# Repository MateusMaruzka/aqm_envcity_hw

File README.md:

# Air Quality Monitoring Board - EnvCity

## Table of Contents
- [Sensors](#sensors)
- [Powering the board](#powering-the-board)
- [Versions](#versions)
- [Contributing](#contributing)

## Introduction
A detailed explanation of your project, its purpose, and what problem it solves.

## Sensors
Your board supports the following sensors:
- 4 electrochemical sensors
- 1 wind speed sensor
- 1 I2C particulate matter sensor
- 1 DHT11/22 sensor

## Powering the board
Your board supports the following energy sources:
- Solar panel
- Battery
- USB-C

## Versions
There's 2 versions, one it's a 2 layer board and the other it's a 4 layer board (This version could easily be made into a 6 layer board and the fab costs on JLCPCB is the same for 4 or 6 layer boards)

## Contributing
If you have any questions, suggestions, or requests, please send an email to mateusroncaglio@alunos.utfpr.edu.br. We welcome contributions to the project!

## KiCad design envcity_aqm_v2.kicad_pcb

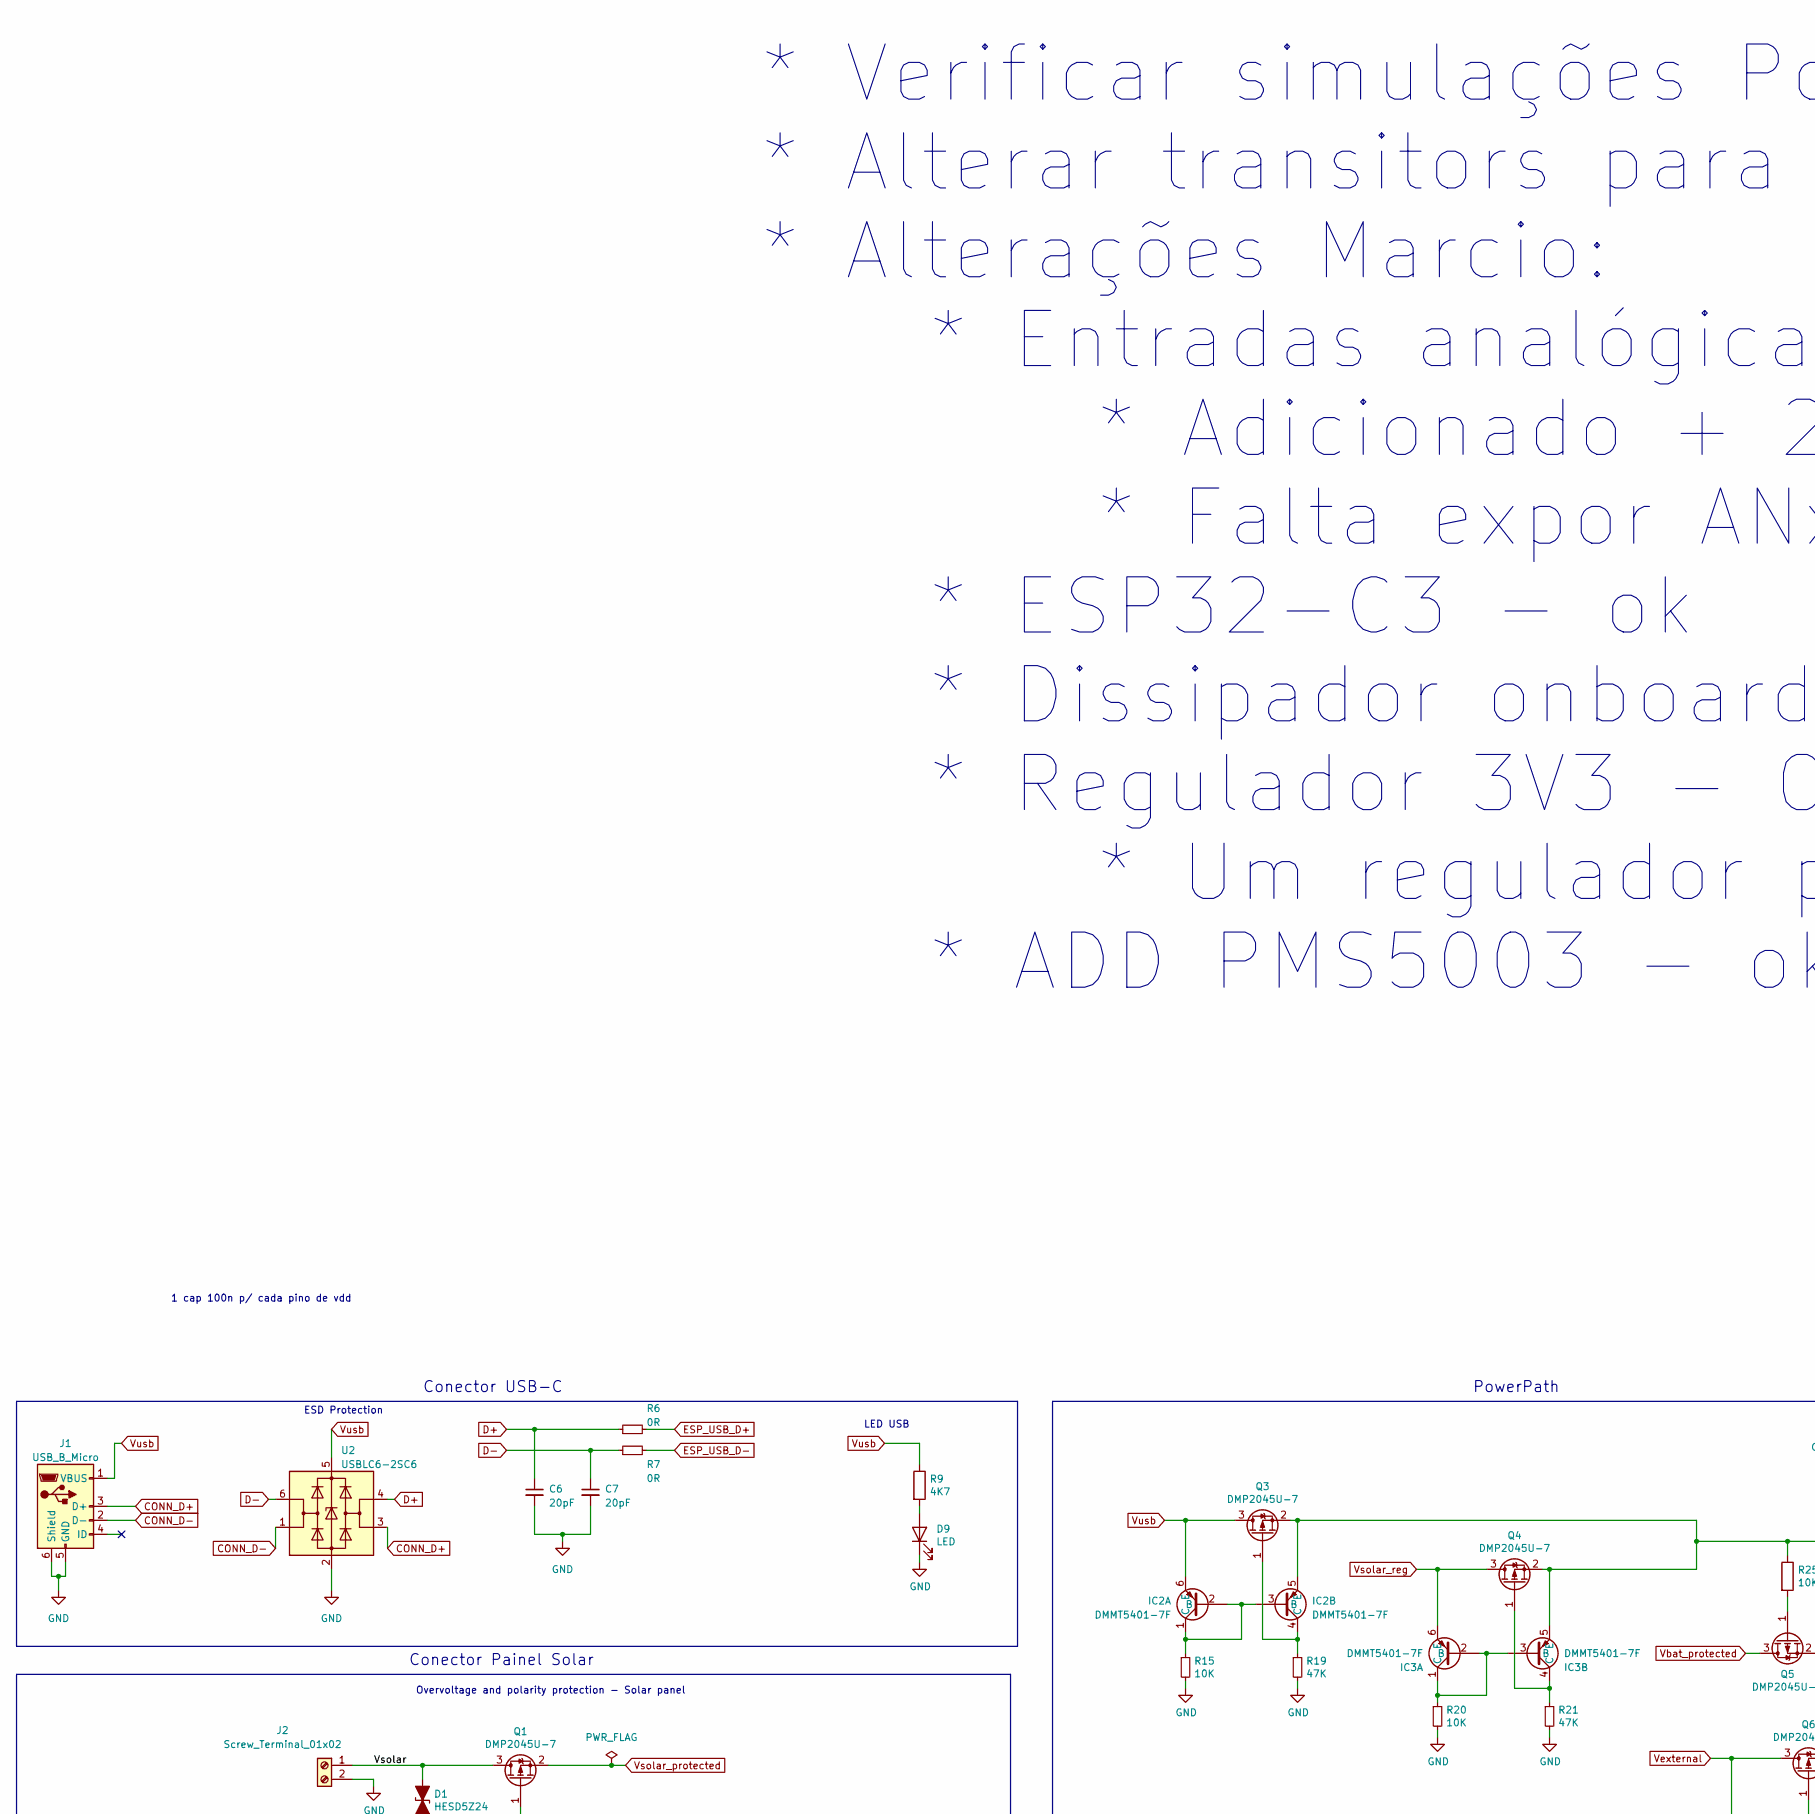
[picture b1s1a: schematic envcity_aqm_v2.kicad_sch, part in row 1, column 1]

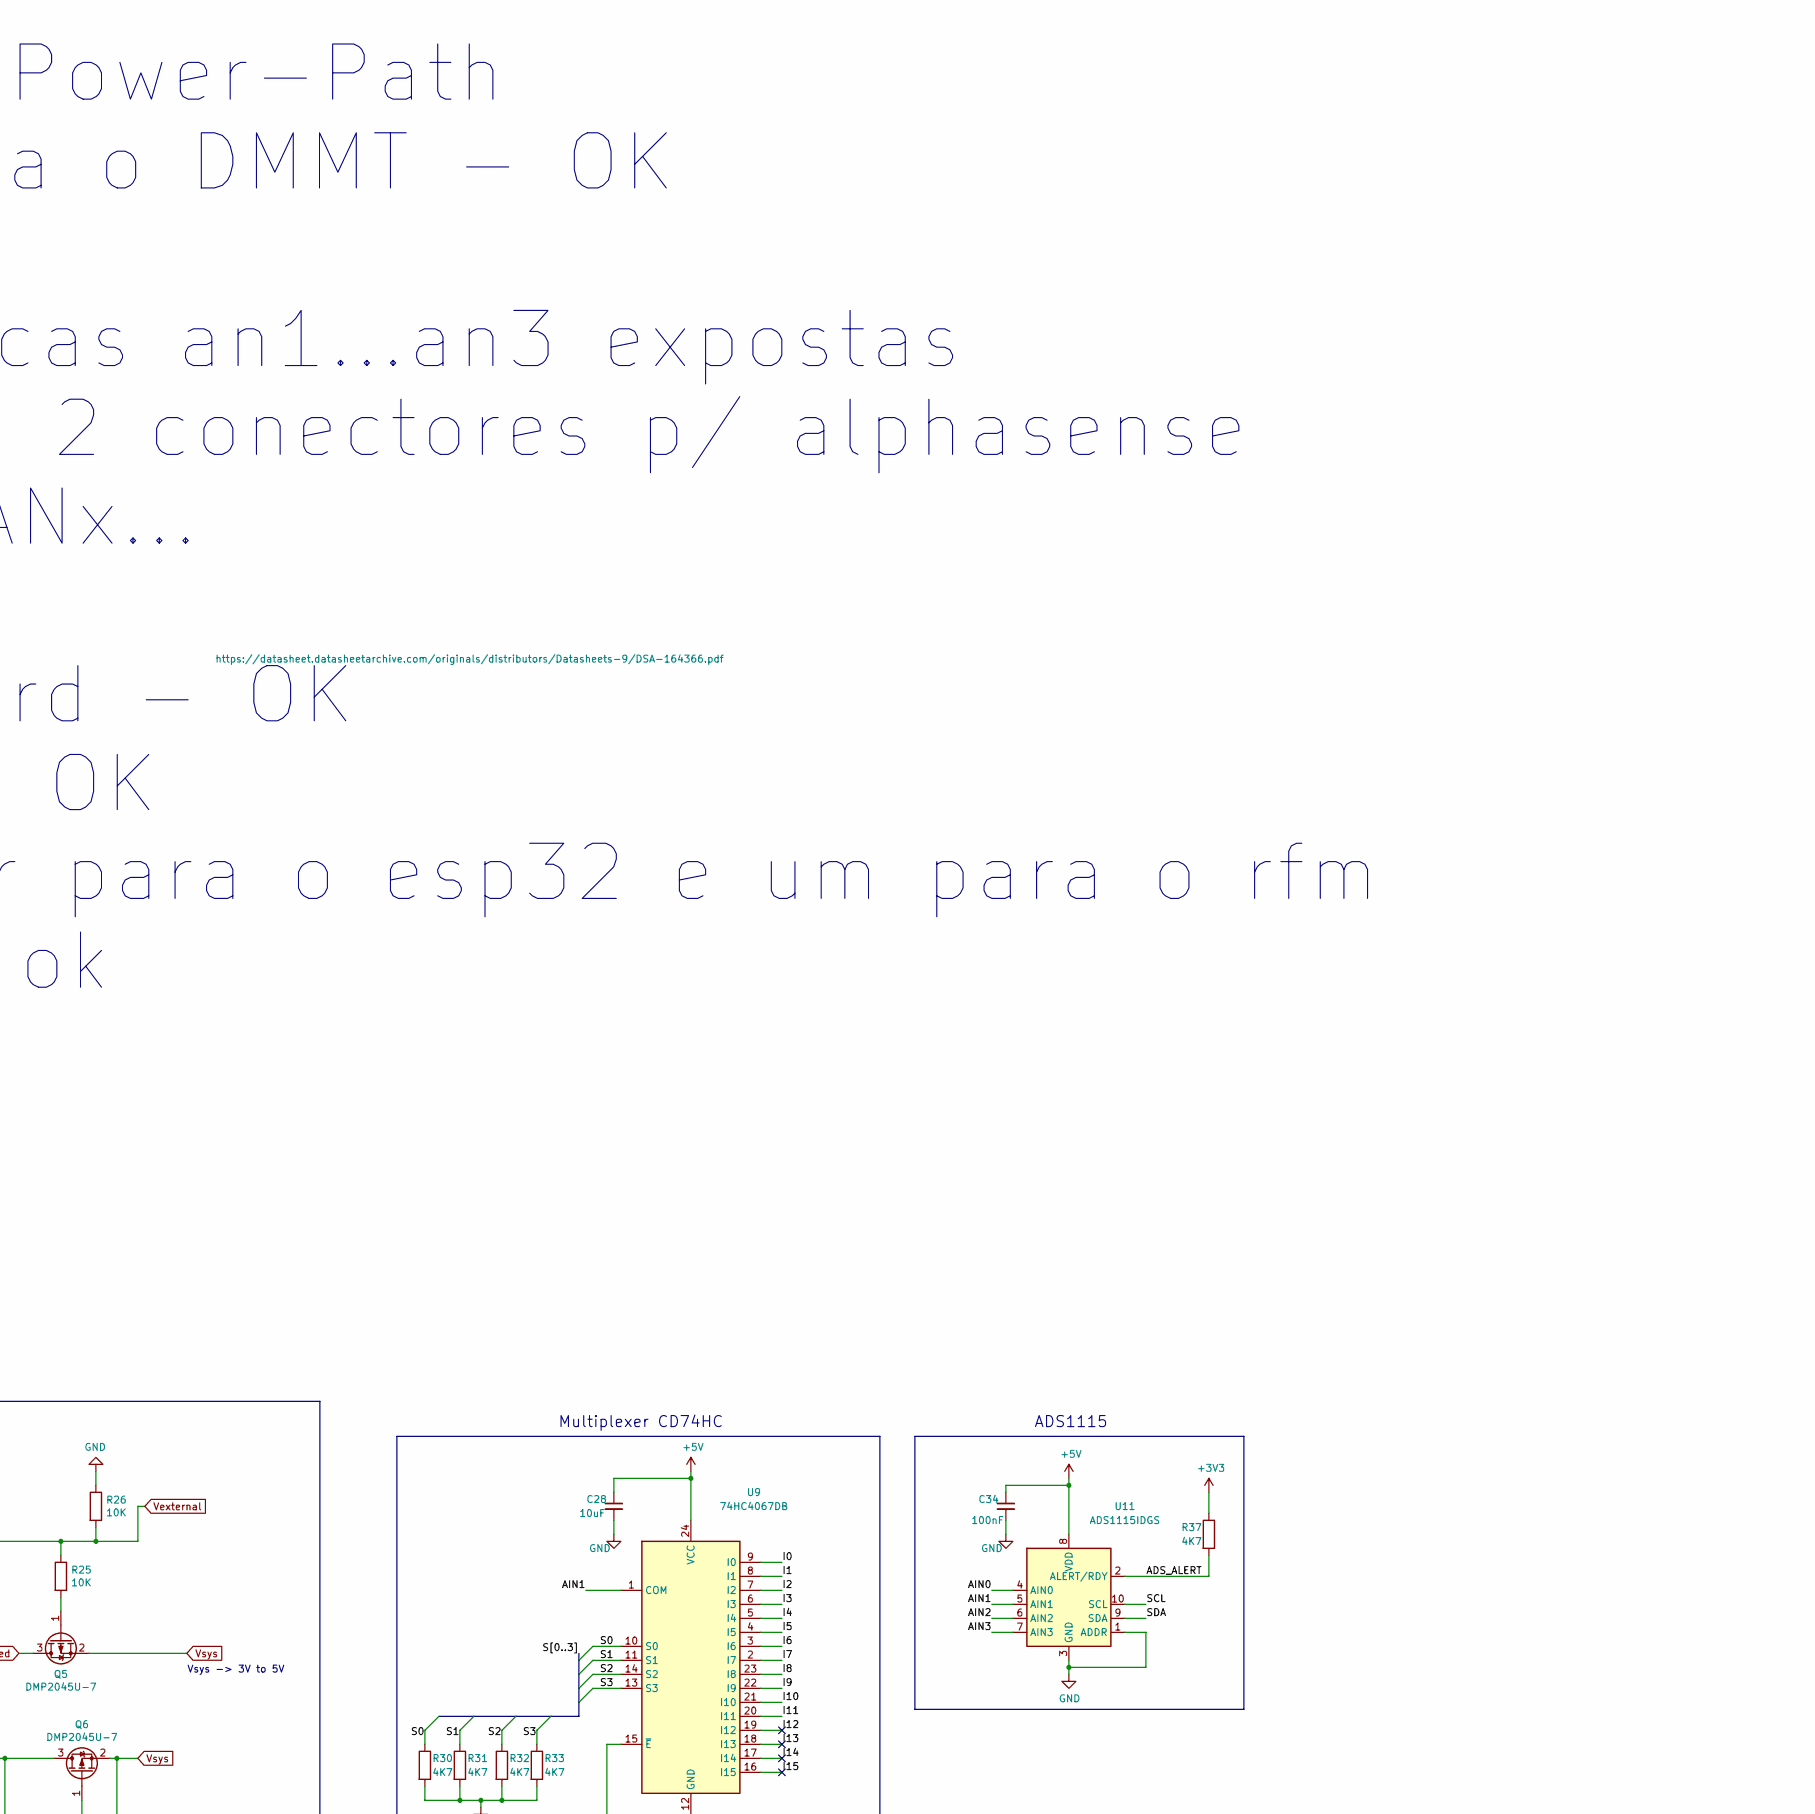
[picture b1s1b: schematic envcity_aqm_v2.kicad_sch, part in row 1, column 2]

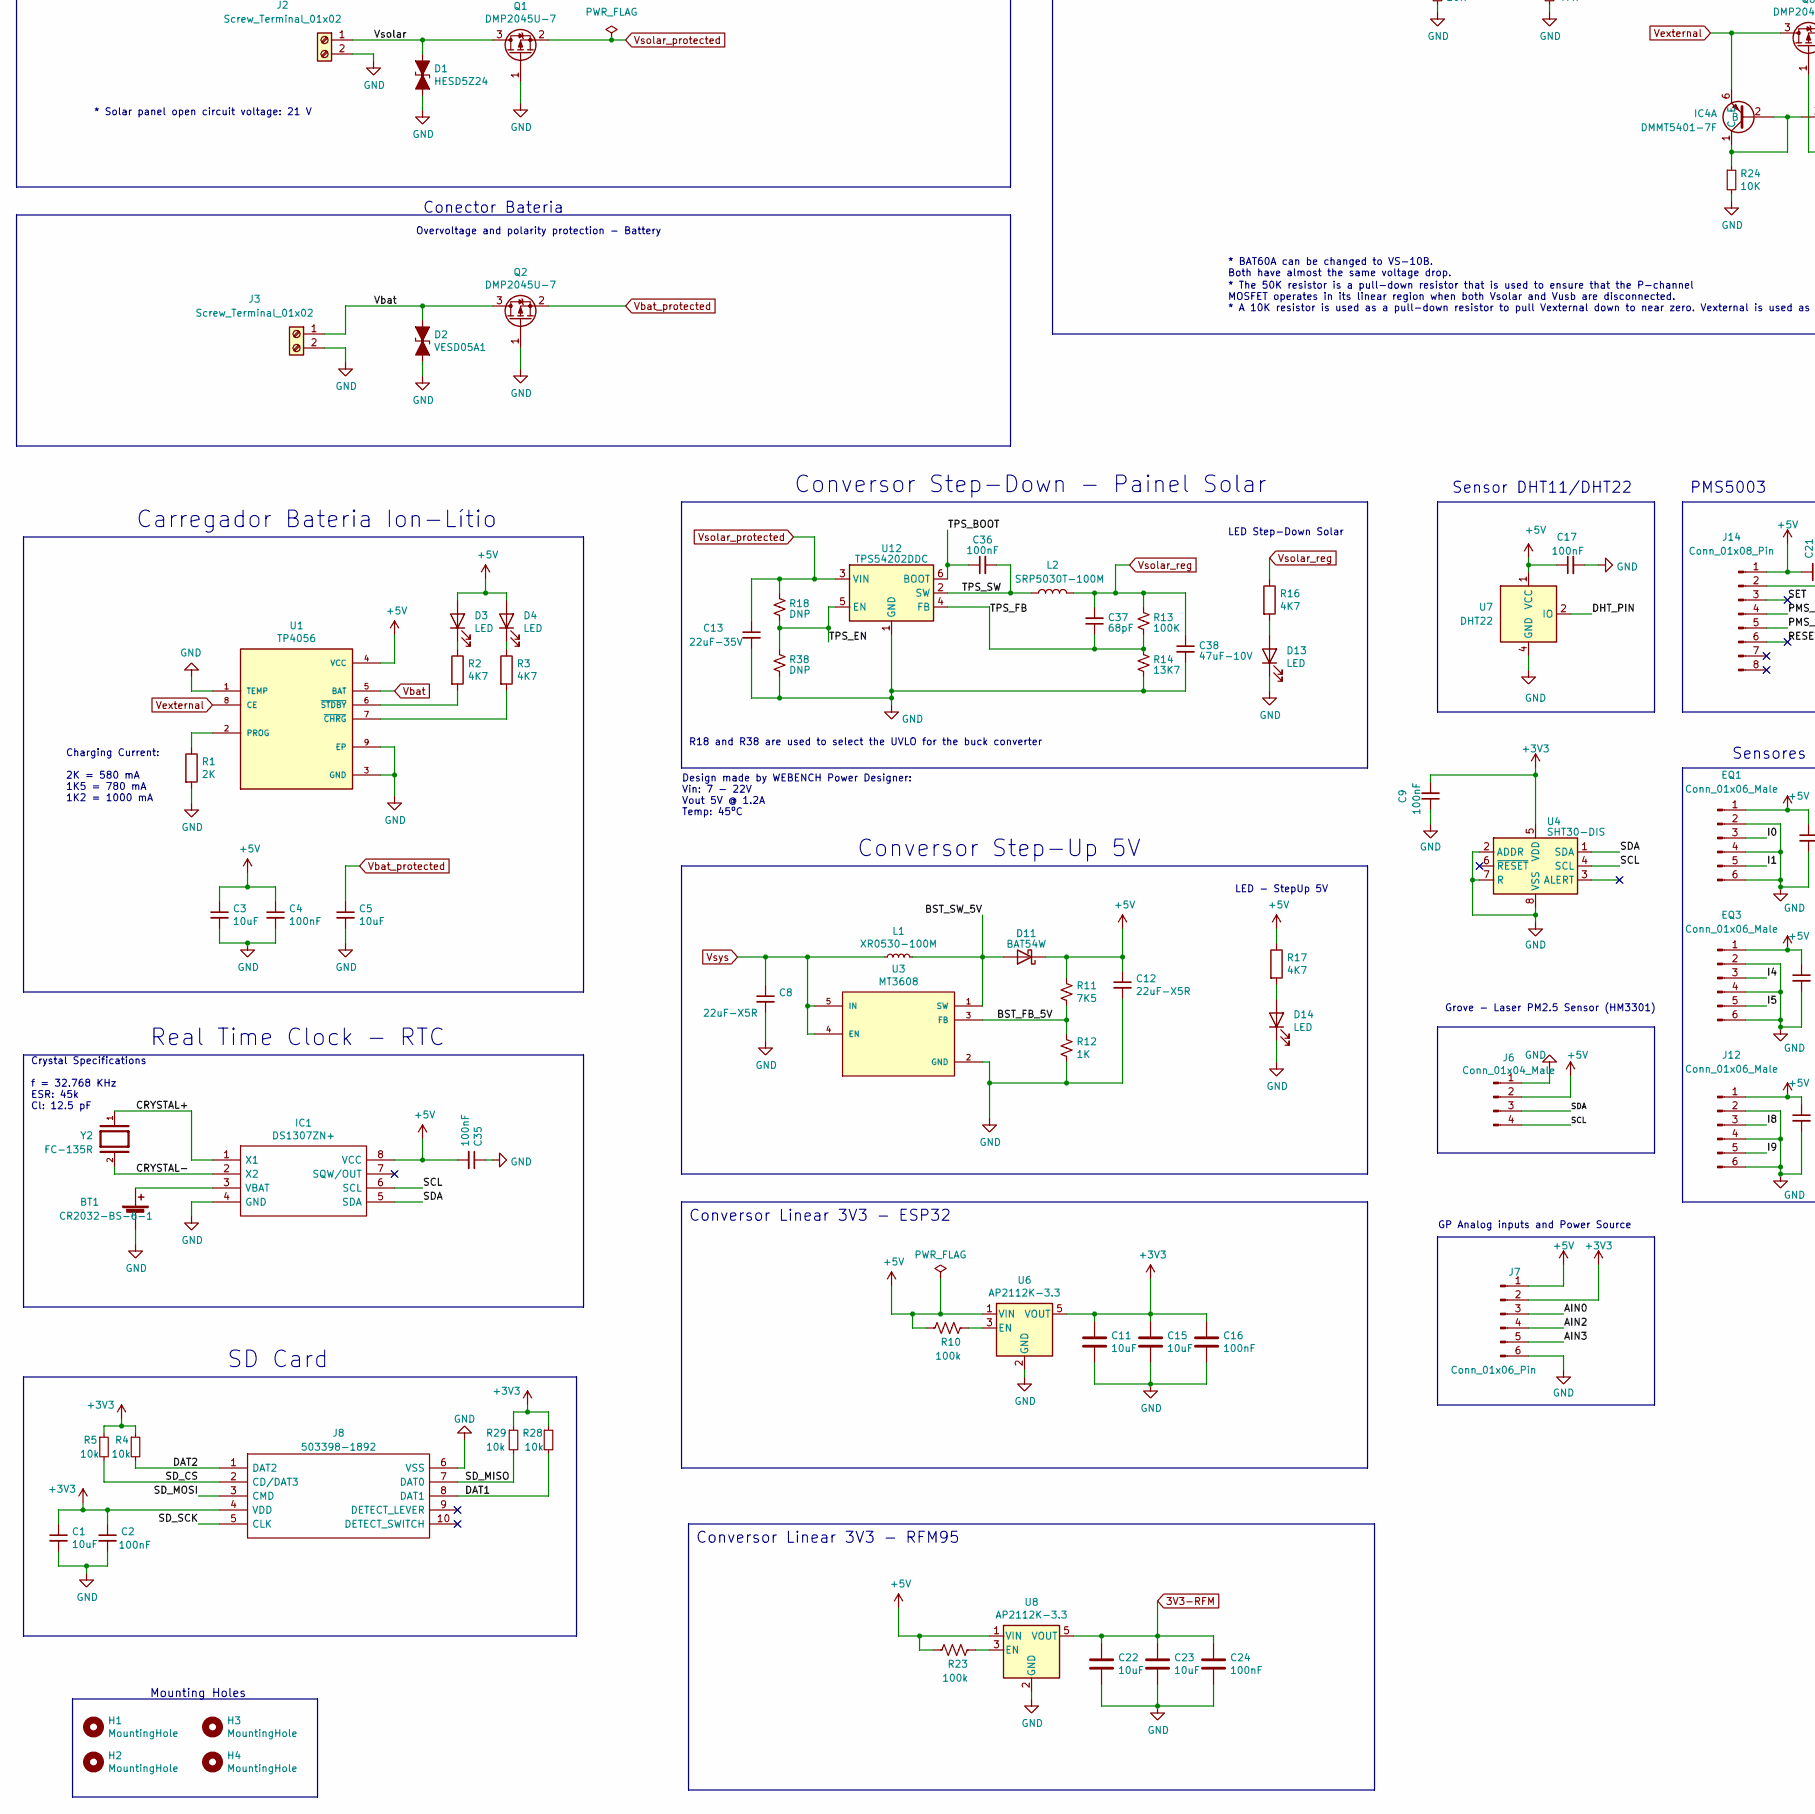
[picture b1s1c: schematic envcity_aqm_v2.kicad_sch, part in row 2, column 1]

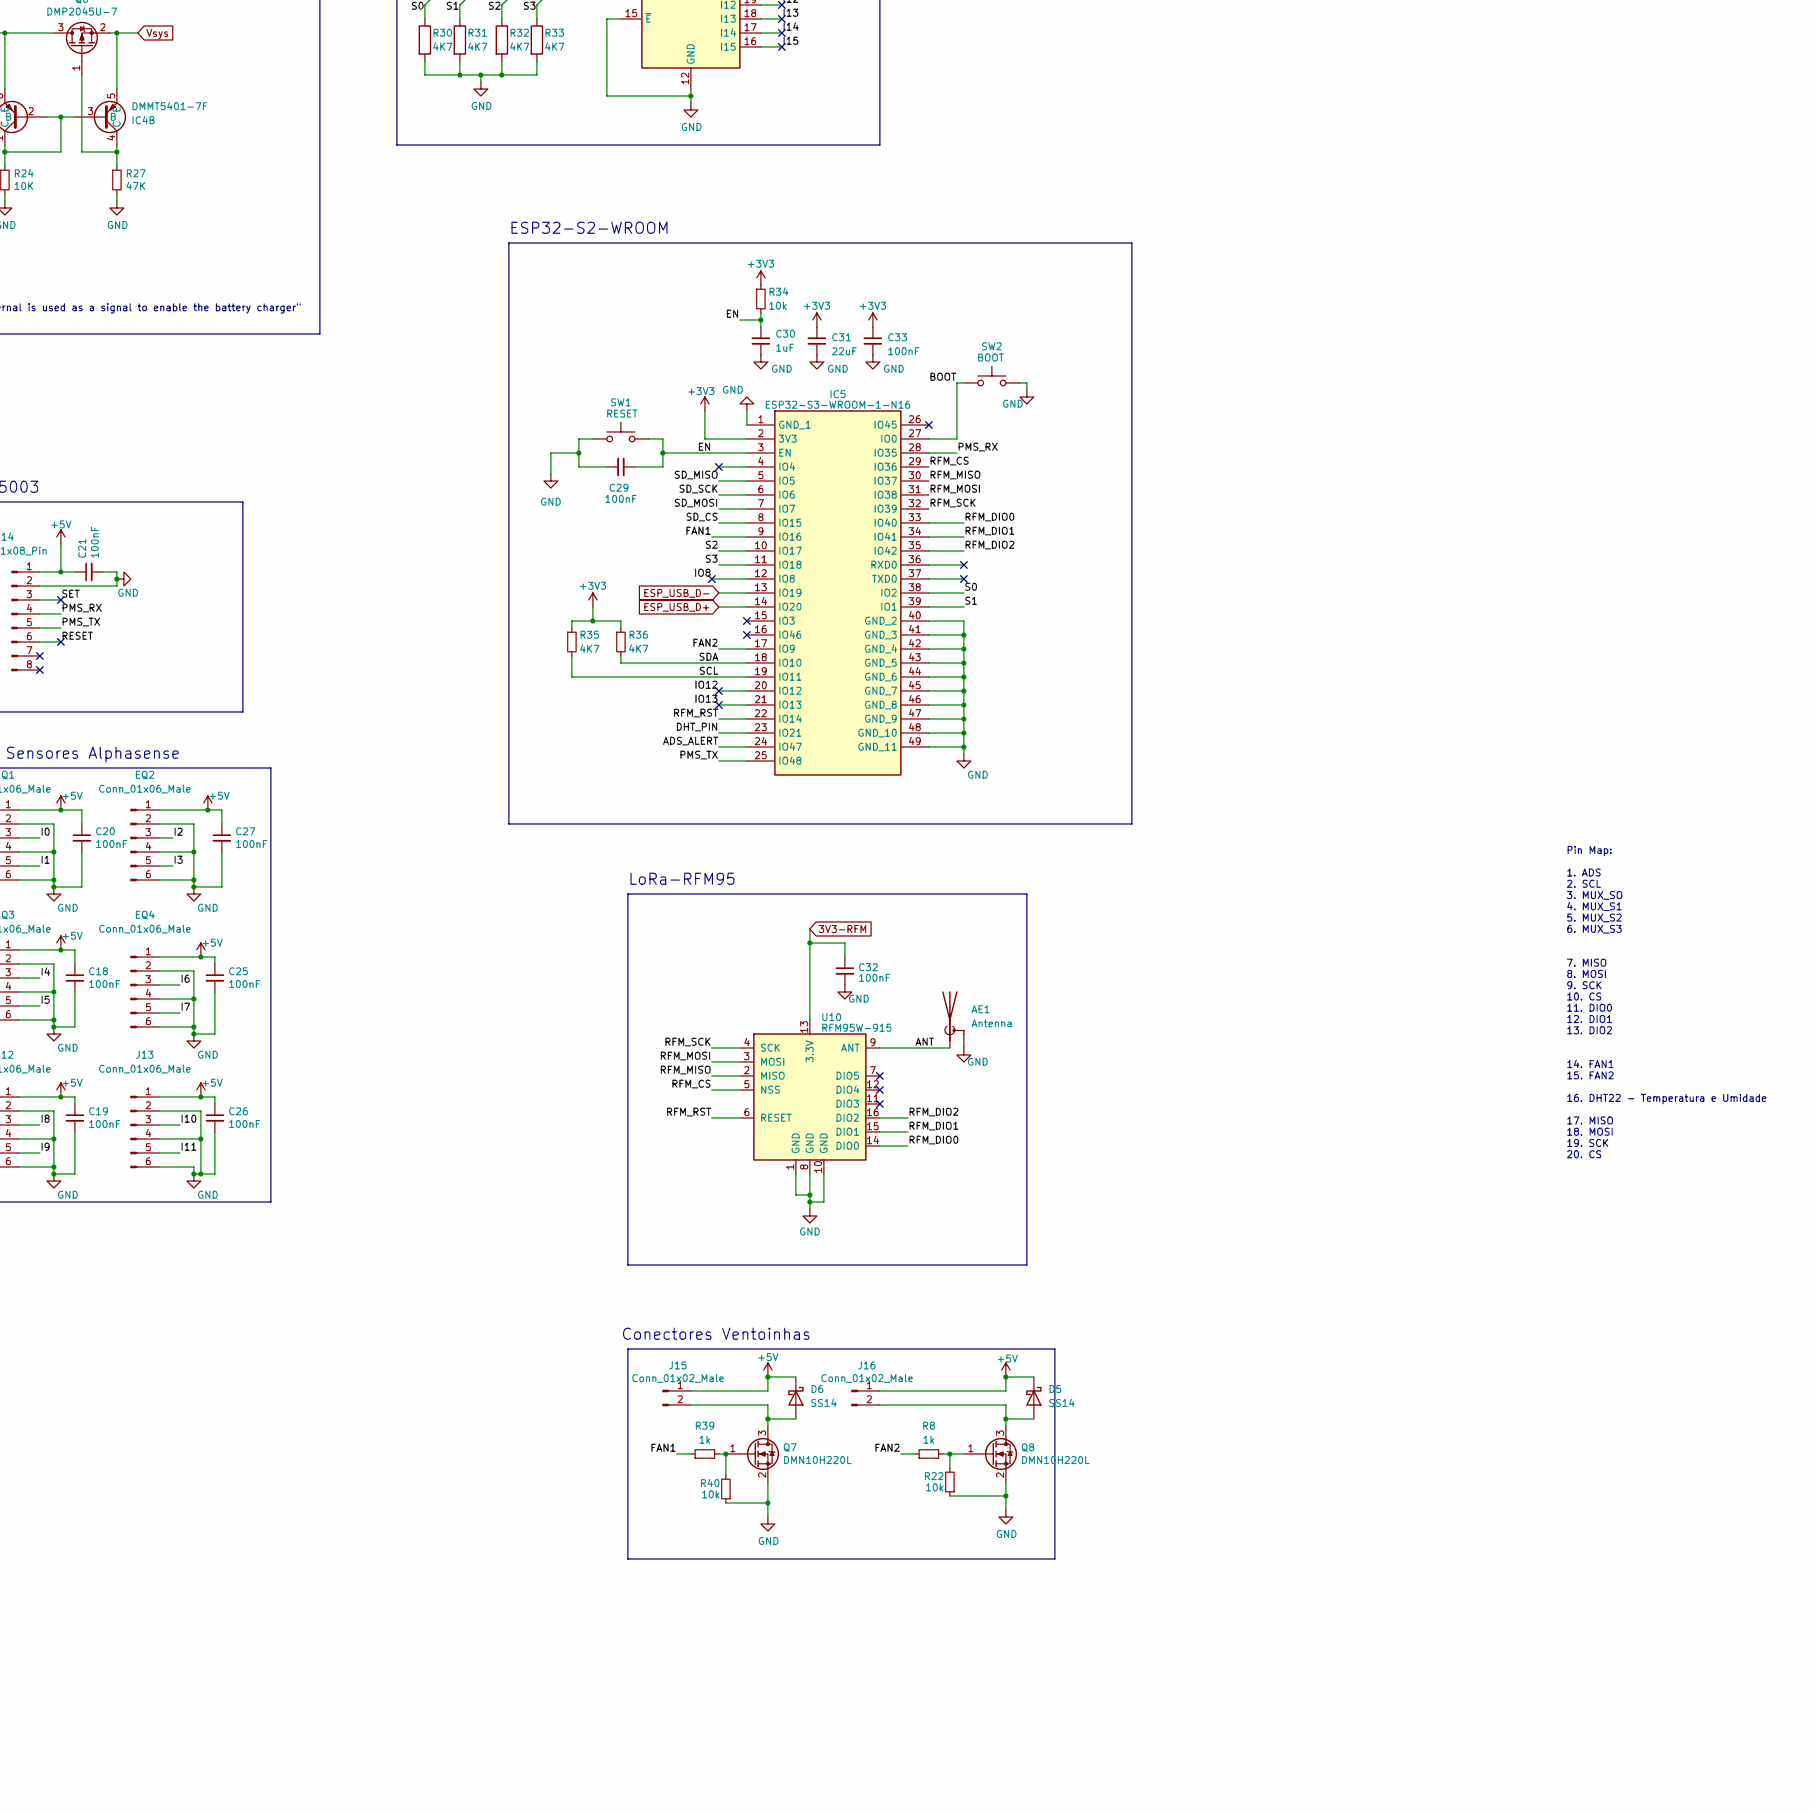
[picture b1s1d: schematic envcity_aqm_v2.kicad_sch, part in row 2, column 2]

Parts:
AE1: Antenna; U.FL_Molex_MCRF_73412-0110_Vertical; LCSC Part # C434806
BT1: CR2032-BS-6-1; BatteryHolder_Keystone_1058_1x2032; LCSC Part # C70377
C1, C15, C28: 10uF; C_0603_1608Metric; LCSC Part # C19702
C2, C9, C16, C17, C18, C19, C20, C21, C25, C26, C27, C29, C33, C34, C35: 100nF; C_0603_1608Metric; LCSC Part # C14663
C3, C5: 10uF; C_0805_2012Metric
C4, C24, C32, C36: 100nF; C_0805_2012Metric; LCSC Part # C14663
C6, C7: 20pF; C_0603_1608Metric
C8, C12: 22uF-X5R; C_0805_2012Metric
C11, C22, C23: 10uF; C_0805_2012Metric; LCSC Part # C19702
C13: 22uF-35V; C_1206_3216Metric; Part # C3216X5R1V226M160AC
C30: 1uF; C_0603_1608Metric
C31: 22uF; C_0603_1608Metric
C37: 68pF; C_0402_1005Metric
C38: 47uF-10V; C_1206_3216Metric; Part # GRM32ER71A476KE15L
D1: HESD5Z24; D_SOD-523; LCSC Part # C3002989
D2: VESD05A1; PESD24VS1ULQZ; LCSC Part # C2844735
D3, D4, D9, D13, D14: LED; LED_0805_2012Metric_Pad1.15x1.40mm_HandSolder
D5, D6: SS14; D_SMA
D11: BAT54W; D_SOD-123; LCSC Part # C915628
EQ1, EQ2, EQ3, EQ4: Conn_01x06_Male; Molex_KK-254_AE-6410-06A_1x06_P2.54mm_Vertical; LCSC Part # C2847672
H1: MountingHole; MountingHole_2.2mm_M2
H2, H3, H4: MountingHole; MountingHole_2.5mm
IC1: DS1307ZN+; SOP-8_3.9x4.9mm_P1.27mm; Mouser Part Number 700-DS1307ZN
IC2, IC3, IC4: DMMT5401-7F; SOT-23-6; Mouser Part Number 621-DMMT5401-7-F
IC5: ESP32-S3-WROOM-1-N16; ESP32S3WROOM1N16; Mouser Part Number 356-ESP32S3WROOM1N16
J1: USB_B_Micro; USB_Micro-B_Molex-105017-0001; JLCPCB Part # C136000
J2, J3: Screw_Terminal_01x02; TerminalBlock_TE_282834-2_1x02_P2.54mm_Horizontal; LCSC Part # C3029316
J6: Conn_01x04_Male; JST_PH_B4B-PH-K_1x04_P2.00mm_Vertical; LCSC Part # C2764213
J7: Conn_01x06_Pin; PinHeader_1x06_P2.54mm_Vertical
J8: 503398-1892; Mouser Part Number 538-503398-1892
J12, J13: Conn_01x06_Male; Molex_KK-254_AE-6410-06A_1x06_P2.54mm_Vertical; LCSC Part # C2847672
J14: Conn_01x08_Pin; Molex_PicoBlade_53047-0810_1x08_P1.25mm_Vertical; JLCPCB Part # C240845
J15: Conn_01x02_Male; Molex_KK-254_AE-6410-02A_1x02_P2.54mm_Vertical; Mfr. Part # 22112022; LCSC Part # C509147
J16: Conn_01x02_Male; Molex_KK-254_AE-6410-02A_1x02_P2.54mm_Vertical; LCSC Part # C509147
L1: XR0530-100M; L_Chilisin_BMRA00050530; LCSC Part # C5307602
L2: SRP5030T-100M; L_Bourns_SRP5030T; Part # SRP5030T-100M; LCSC Part # C189932
Q1, Q2, Q3, Q4, Q5, Q6: DMP2045U-7; SOT-23; LCSC Part # C459541
Q7, Q8: DMN10H220L; SOT-23; LCSC Part # C5122013
R1: 2K; R_0603_1608Metric
R2, R3, R16, R17, R35, R36: 4K7; R_0603_1608Metric; LCSC Part # C23162
R4, R5, R28, R29, R34: 10k; R_0402_1005Metric; LCSC Part # C25744
R6, R7: 0R; R_0603_1608Metric
R8, R39: 1k; R_0805_2012Metric
R9: 4K7; R_0805_2012Metric
R10, R23: 100k; R_0603_1608Metric; LCSC Part # C25804
R11: 7K5; R_0603_1608Metric
R12: 1K; R_0603_1608Metric
R13: 100K; R_0402_1005Metric
R14: 13K7; R_0402_1005Metric
R15, R20, R24, R25, R26: 10K; R_0603_1608Metric; LCSC Part # C25804
R18, R38: DNP; R_0603_1608Metric
R19, R27: 47K; R_0603_1608Metric
R21: 47K; R_0805_2012Metric
R22, R40: 10k; R_0805_2012Metric
R30, R31, R32, R33, R37: 4K7; R_0402_1005Metric; LCSC Part # C25900
SW1: RESET; SW_SPST_PTS810; JLCPCB Part # C221897
SW2: BOOT; SW_SPST_PTS810; JLCPCB Part # C221897
U1: TP4056; SOP127P600X175-9N; LCSC Part # C382139
U2: USBLC6-2SC6; SOT-23-6; LCSC Part # C7519
U3: MT3608; SOT-23-6_Handsoldering; PARTREV 1.0; JLCPCB Part # C84817
U4: SHT30-DIS; Sensirion_DFN-8-1EP_2.5x2.5mm_P0.5mm_EP1.1x1.7mm; JLCPCB Part # C2687423
U6, U8: AP2112K-3.3; SOT-23-5; LCSC Part # C51118
U7: DHT22; Aosong_DHT11_5.5x12.0_P2.54mm
U9: 74HC4067DB; SSOP-24_5.3x8.2mm_P0.65mm; LCSC Part # C97702
U10: RFM95W-915; HOPERF_RFM9XW_SMD; LCSC Part # C2844473
U11: ADS1115IDGS; TSSOP-10_3x3mm_P0.5mm; JLCPCB Part # C37593
U12: TPS54202DDC; SOT-23-6
Y2: FC-135R; Crystal_SMD_3215-2Pin_3.2x1.5mm; JLCPCB Part # C94276

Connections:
3V3-RFM: C22.1, C23.1, C24.1, C32.1, U8.5 (VOUT), U10.13 (3.3V)
+3V3: C1.1, C2.1, C9.2, C11.1, C15.1, C16.1, C31.1, C33.1, IC5.2 (3V3), J7.2, J8.4 (VDD), R4.1, R5.1, R28.1, R29.1, R34.1, R35.1, R36.1, R37.1, U4.5 (VDD), U6.5 (VOUT)
+5V: C3.1, C4.1, C12.1, C17.1, C18.1, C19.1, C20.1, C21.1, C25.1, C26.1, C27.1, C28.1, C34.1, C35.2, D3.2 (A), D4.2 (A), D5.1 (K), D6.1 (K), D11.1 (K), EQ1.1, EQ2.1, EQ3.1, EQ4.1, IC1.8 (VCC), J6.2, J7.1, J12.1, J13.1, J14.1, J15.1, J16.1, R10.1, R11.1, R17.1, R23.1, U1.4 (VCC), U6.1 (VIN), U7.1 (VCC), U8.1 (VIN), U9.24 (VCC), U11.8 (VDD)
/ADS_ALERT: IC5.24 (IO47), R37.2, U11.2 (ALERT/RDY)
/AIN0: J7.3, U11.4 (AIN0)
/AIN1: U9.1 (COM), U11.5 (AIN1)
/AIN2: J7.4, U11.6 (AIN2)
/AIN3: J7.5, U11.7 (AIN3)
/ANT: AE1.1 (A), U10.9 (ANT)
/BOOT: IC5.27 (IO0), SW2.1
/BST_FB_5V: R11.2, R12.1, U3.3 (FB)
/BST_SW_5V: D11.2 (A), L1.2, U3.1 (SW)
/CRYSTAL+: IC1.1 (X1), Y2.1
/CRYSTAL-: IC1.2 (X2), Y2.2
/DAT1: J8.8 (DAT1), R28.2
/DAT2: J8.1 (DAT2), R4.2
/DHT_PIN: IC5.23 (IO21), U7.2 (IO)
/EN: C29.1, C30.1, IC5.3 (EN), R34.2, SW1.2
/FAN1: IC5.9 (IO16), R39.1
/FAN2: IC5.17 (IO9), R8.1
/I0: EQ1.3, U9.9 (I0)
/I1: EQ1.5, U9.8 (I1)
/I2: EQ2.3, U9.7 (I2)
/I3: EQ2.5, U9.6 (I3)
/I4: EQ3.3, U9.5 (I4)
/I5: EQ3.5, U9.4 (I5)
/I6: EQ4.3, U9.3 (I6)
/I7: EQ4.5, U9.2 (I7)
/I8: J12.3, U9.23 (I8)
/I9: J12.5, U9.22 (I9)
/I10: J13.3, U9.21 (I10)
/I11: J13.5, U9.20 (I11)
/I12: U9.19 (I12)
/I13: U9.18 (I13)
/I14: U9.17 (I14)
/I15: U9.16 (I15)
/IO8: IC5.12 (IO8)
/IO12: IC5.20 (IO12)
/IO13: IC5.21 (IO13)
/PMS_RX: IC5.28 (IO35), J14.4
/PMS_TX: IC5.25 (IO48), J14.5
/RESET: J14.6
/RFM_CS: IC5.29 (IO36), U10.5 (NSS)
/RFM_DIO0: IC5.33 (IO40), U10.14 (DIO0)
/RFM_DIO1: IC5.34 (IO41), U10.15 (DIO1)
/RFM_DIO2: IC5.35 (IO42), U10.16 (DIO2)
/RFM_MISO: IC5.30 (IO37), U10.2 (MISO)
/RFM_MOSI: IC5.31 (IO38), U10.3 (MOSI)
/RFM_RST: IC5.22 (IO14), U10.6 (RESET)
/RFM_SCK: IC5.32 (IO39), U10.4 (SCK)
/S0: IC5.38 (IO2), R30.1, U9.10 (S0)
/S1: IC5.39 (IO1), R31.1, U9.11 (S1)
/S2: IC5.10 (IO17), R32.1, U9.14 (S2)
/S3: IC5.11 (IO18), R33.1, U9.13 (S3)
/SCL: IC1.6 (SCL), IC5.19 (IO11), J6.4, R35.2, U4.4 (SCL), U11.10 (SCL)
/SDA: IC1.5 (SDA), IC5.18 (IO10), J6.3, R36.2, U4.1 (SDA), U11.9 (SDA)
/SD_CS: IC5.8 (IO15), J8.2 (CD/DAT3), R5.2
/SD_MISO: IC5.5 (IO5), J8.7 (DAT0), R29.2
/SD_MOSI: IC5.7 (IO7), J8.3 (CMD)
/SD_SCK: IC5.6 (IO6), J8.5 (CLK)
/SET: J14.3
/TPS_BOOT: C36.1, U12.6 (BOOT)
/TPS_EN: R18.2, R38.1, U12.5 (EN)
/TPS_FB: C37.1, R13.2, R14.1, U12.4 (FB)
/TPS_SW: C36.2, L2.1, U12.2 (SW)
/Vsolar: D1.1 (A1), J2.1, Q1.3 (D)
CONN_D+: J1.3 (D+), U2.3 (I/O2)
CONN_D-: J1.2 (D-), U2.1 (I/O1)
D+: C6.1, R6.1, U2.4 (I/O2)
D-: C7.1, R7.1, U2.6 (I/O1)
ESP_USB_D+: IC5.14 (IO20), R6.2
ESP_USB_D-: IC5.13 (IO19), R7.2
GND: AE1.2 (Shield), BT1.2 (-), C1.2, C2.2, C3.2, C4.2, C5.2, C6.2, C7.2, C8.2, C9.1, C11.2, C12.2, C13.2, C15.2, C16.2, C17.2, C18.2, C19.2, C20.2, C21.2, C22.2, C23.2, C24.2, C25.2, C26.2, C27.2, C28.2, C29.2, C30.2, C31.2, C32.2, C33.2, C34.2, C35.1, C38.2, D1.2 (A2), D2.2 (A2), D9.1 (K), D13.1 (K), D14.1 (K), EQ1.2, EQ1.4, EQ1.6, EQ2.2, EQ2.4, EQ2.6, EQ3.2, EQ3.4, EQ3.6, EQ4.2, EQ4.4, EQ4.6, IC1.4 (GND), IC5.1 (GND_1), IC5.40 (GND_2), IC5.41 (GND_3), IC5.42 (GND_4), IC5.43 (GND_5), IC5.44 (GND_6), IC5.45 (GND_7), IC5.46 (GND_8), IC5.47 (GND_9), IC5.48 (GND_10), IC5.49 (GND_11), J1.5 (GND), J1.6 (Shield), J2.2, J3.2, J6.1, J7.6, J8.6 (VSS), J12.2, J12.4, J12.6, J13.2, J13.4, J13.6, J14.2, Q1.1 (G), Q2.1 (G), Q7.2 (S), Q8.2 (S), R1.2, R12.2, R14.2, R15.2, R19.2, R20.2, R21.2, R22.1, R24.2, R26.1, R27.2, R30.2, R31.2, R32.2, R33.2, R38.2, R40.1, SW1.1, SW2.2, U1.1 (TEMP), U1.3 (GND), U1.9 (EP), U2.2 (GND), U3.2 (GND), U4.2 (ADDR), U4.7 (R), U4.8 (VSS), U4.9 (VSS), U6.2 (GND), U7.4 (GND), U8.2 (GND), U9.12 (GND), U9.15 (~E), U10.1 (GND), U10.8 (GND), U10.10 (GND), U11.1 (ADDR), U11.3 (GND), U12.1 (GND)
unnamed: BT1.1 (+), IC1.3 (VBAT)
unnamed: D3.1 (K), R2.1
unnamed: D4.1 (K), R3.1
unnamed: D5.2 (A), J16.2, Q8.3 (D)
unnamed: D6.2 (A), J15.2, Q7.3 (D)
unnamed: D9.2 (A), R9.2
unnamed: D13.2 (A), R16.2
unnamed: D14.2 (A), R17.2
unnamed: IC2.1 (C), IC2.2 (B), IC2.3 (B), R15.1
unnamed: IC2.4 (C), Q3.1 (G), R19.1
unnamed: IC3.1 (C), IC3.2 (B), IC3.3 (B), R20.1
unnamed: IC3.4 (C), Q4.1 (G), R21.1
unnamed: IC4.1 (C), IC4.2 (B), IC4.3 (B), R24.1
unnamed: IC4.4 (C), Q6.1 (G), R27.1
unnamed: Q5.1 (G), R25.2
unnamed: Q7.1 (G), R39.2, R40.2
unnamed: Q8.1 (G), R8.2, R22.2
unnamed: R1.1, U1.2 (PROG)
unnamed: R3.2, U1.7 (~CHRG)
unnamed: R2.2, U1.6 (~STDBY)
unnamed: R10.2, U6.3 (EN)
unnamed: R23.2, U8.3 (EN)
Vbat: D2.1 (A1), J3.1, Q2.3 (D), U1.5 (BAT)
Vbat_protected: C5.1, Q2.2 (S), Q5.3 (D)
Vexternal: IC2.5 (E), IC3.5 (E), IC4.6 (E), Q3.2 (S), Q4.2 (S), Q6.3 (D), R25.1, R26.2, U1.8 (CE)
Vsolar_protected: C13.1, Q1.2 (S), R18.1, U12.3 (VIN)
Vsolar_reg: C37.2, C38.1, IC3.6 (E), L2.2, Q4.3 (D), R13.1, R16.1
Vsys: C8.1, IC4.5 (E), L1.1, Q5.2 (S), Q6.2 (S), U3.4 (EN), U3.5 (IN)
Vusb: IC2.6 (E), J1.1 (VBUS), Q3.3 (D), R9.1, U2.5 (VBUS)

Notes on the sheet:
Conector Bateria
* The 50K resistor is a pull-down resistor that is used to ensure that the P-channel MOSFET operates in its linear region when both Vsolar and Vusb are disconnected. * A 10K resistor is used as a pull-down resistor to pull Vexternal down to near zero. Vexternal is used as a signal to enable the bat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
Sensor DHT11/DHT22
LED Step-Down Solar
Conversor Linear 3V3 - RFM95
Pin Map: 1. ADS 2. SCL 3. MUX_SO 4. MUX_S1 5. MUX_S2 6. MUX_S3 7. MISO 8. MOSI 9. SCK 10. CS 11. DIO0 12. DIO1 13. DIO2 14. FAN1 15. FAN2 16. DHT22 - Temperatura e Umidade 17. MISO 18. MOSI 19. SCK 20. CS
Overvoltage and polarity protection - Solar panel
ESD Protection
Overvoltage and polarity protection - Battery
Vsys -> 3V to 5V
Real Time Clock - RTC
Mounting Holes
PMS5003
* BAT60A can be changed to VS-10B. Both have almost the same voltage drop.
Conversor Linear 3V3 - ESP32
Conector Painel Solar
Design made by WEBENCH Power Designer: Vin: 7 - 22V Vout 5V @ 1.2A Temp: 45ºC
Charging Current: 2K = 580 mA 1K5 = 780 mA 1K2 = 1000 mA
Conector USB-C
LED USB
LED - StepUp 5V
SD Card
ADS1115
* Solar panel open circuit voltage: 21 V
Conversor Step-Down - Painel Solar
Multiplexer CD74HC
* Verificar simulações Power-Path * Alterar transitors para o DMMT - OK * Alterações Marcio: * Entradas analógicas an1...an3 expostas * Adicionado + 2 conectores p/ alphasense * Falta expor ANx... * ESP32-C3 - ok * Dissipador onboard - OK * Regulador 3V3 - OK * Um regulador para o esp32 e um para o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
PowerPath
Conversor Step-Up 5V
Carregador Bateria Ion-Lítio
ESP32-S2-WROOM
Grove - Laser PM2.5 Sensor (HM3301)
GP Analog inputs and Power Source
LoRa-RFM95
1 cap 100n p/ cada pino de vdd
Crystal Specifications f = 32.768 KHz ESR: 45k Cl: 12.5 pF
R18 and R38 are used to select the UVLO for the buck converter
Conectores Ventoinhas
Sensores Alphasense

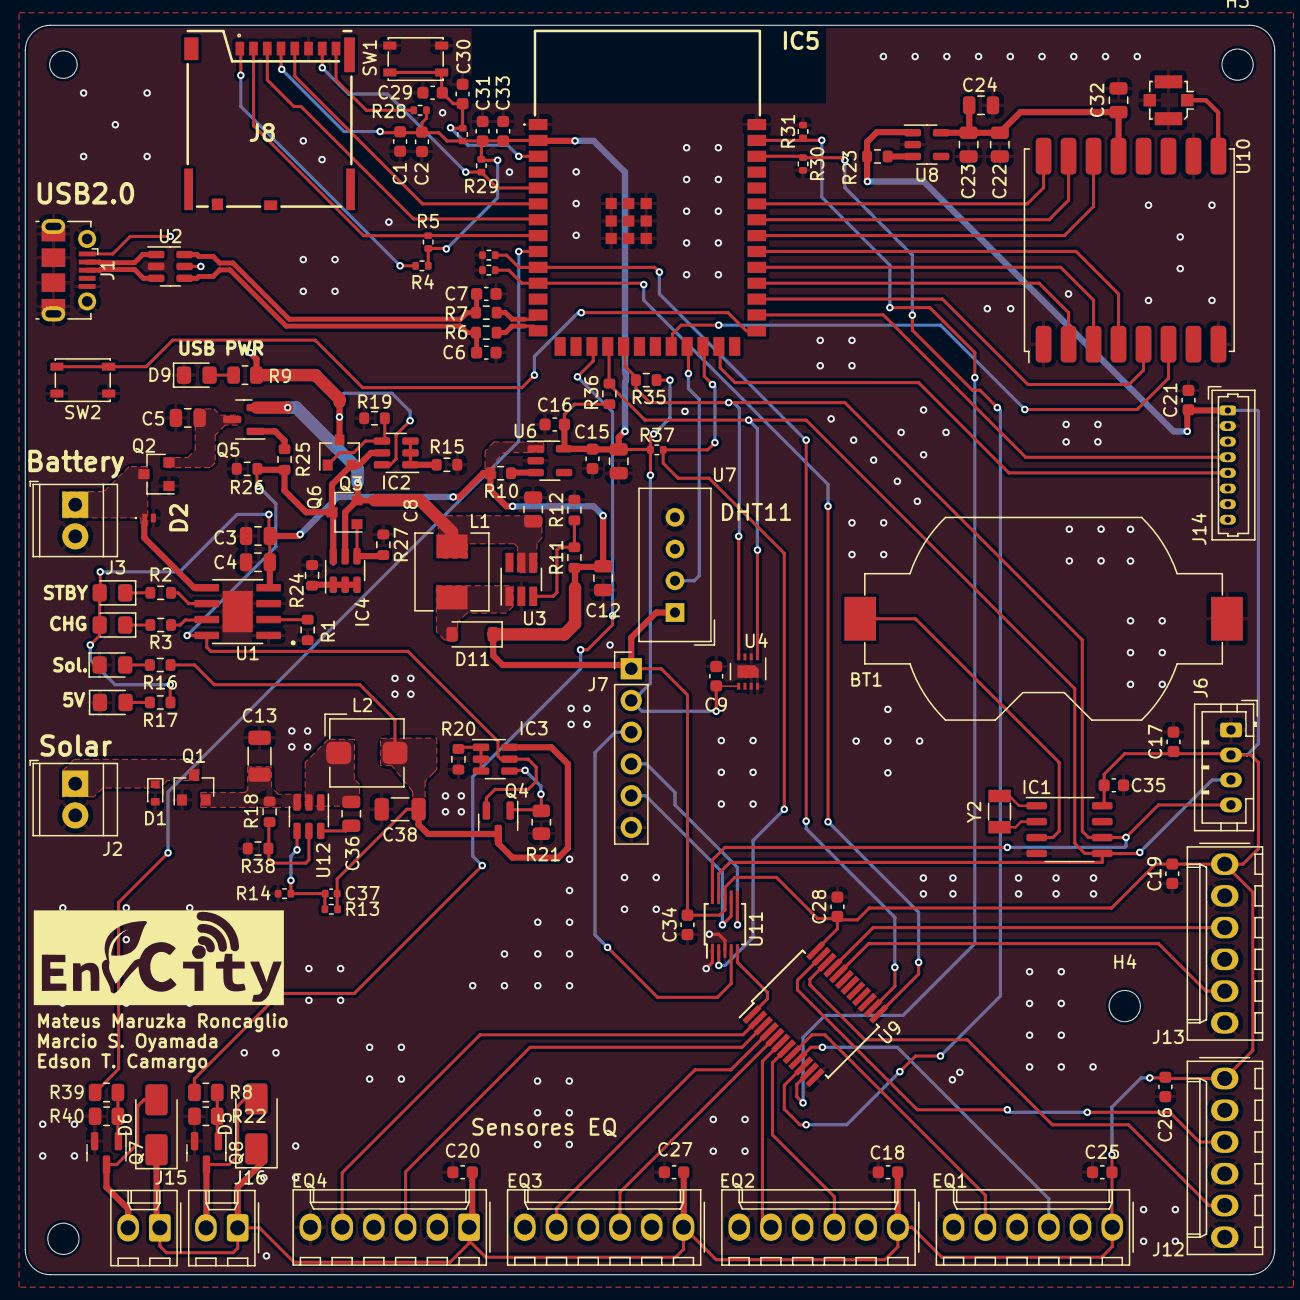
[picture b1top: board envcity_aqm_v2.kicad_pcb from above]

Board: 2 copper layers, 100.0 x 100.0 mm, 136 parts (0 on the bottom side), 93 nets.

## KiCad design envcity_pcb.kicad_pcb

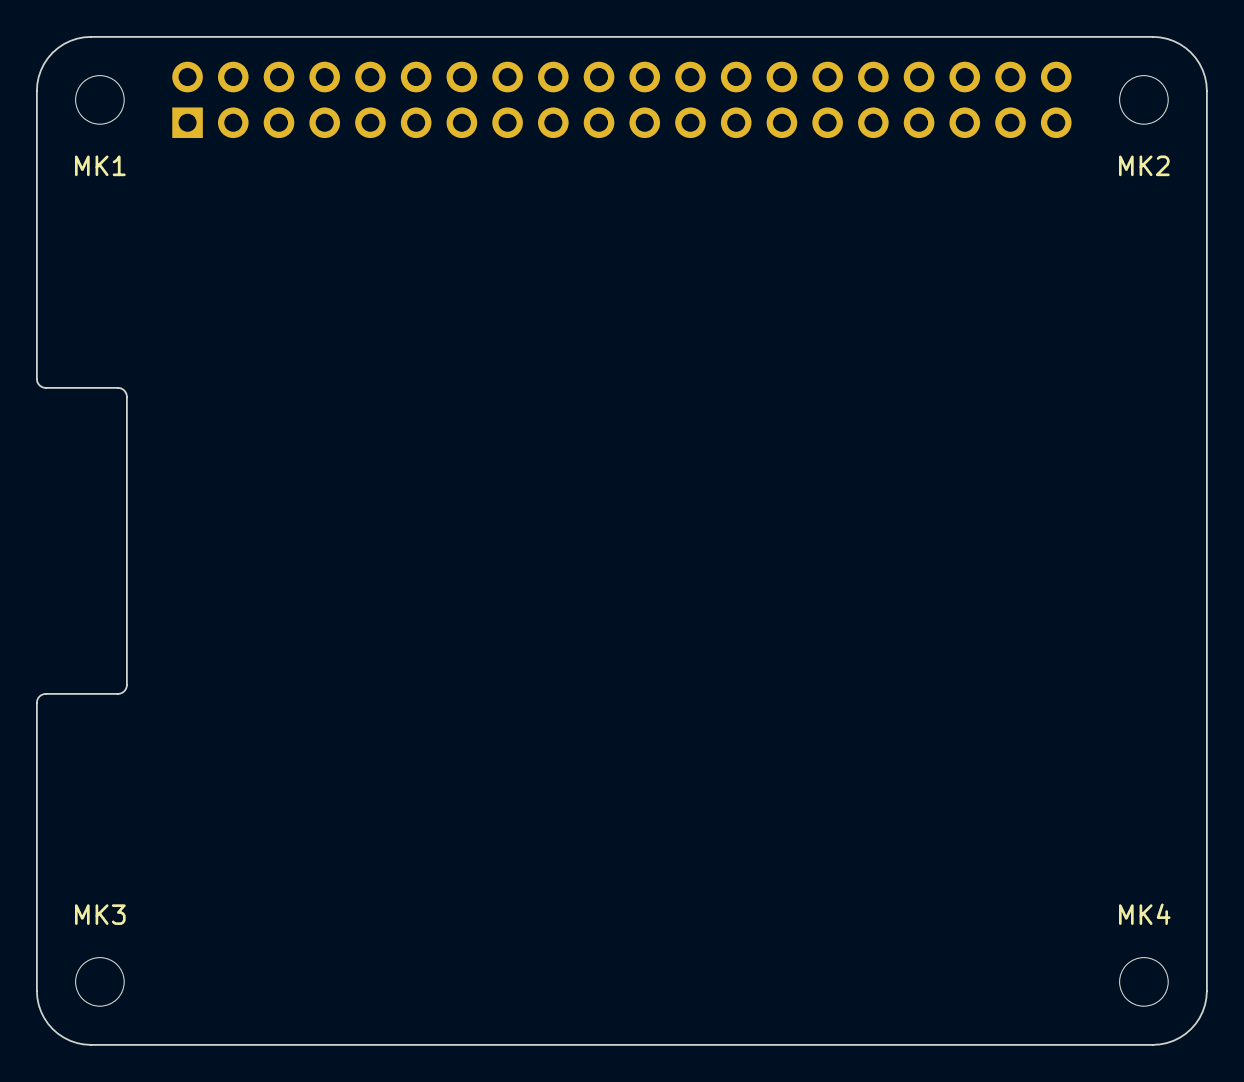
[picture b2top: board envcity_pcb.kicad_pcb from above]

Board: 2 copper layers, 65.0 x 56.0 mm, 5 parts (1 on the bottom side), 3 nets, no tracks yet.

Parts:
MK1, MK2, MK3, MK4: M2.5; MountingHole_2.7mm_M2.5
P1: Conn_02x20_Odd_Even; PinSocket_2x20_P2.54mm_Vertical

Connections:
+3V3: P1.1, P1.17
+5V: P1.2, P1.4
GND: P1.6, P1.9, P1.14, P1.20, P1.25, P1.30, P1.34, P1.39
